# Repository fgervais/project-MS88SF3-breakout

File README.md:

# MS88SF3 Breakout Board

## Objective

Try out the nRF52840 module from Minew.

## Power Consumption

### Sleep - Full RAM retention - GPIO wake-up

Average: 2.78 μA

## Price

## PCB

## BOM

### Firmware

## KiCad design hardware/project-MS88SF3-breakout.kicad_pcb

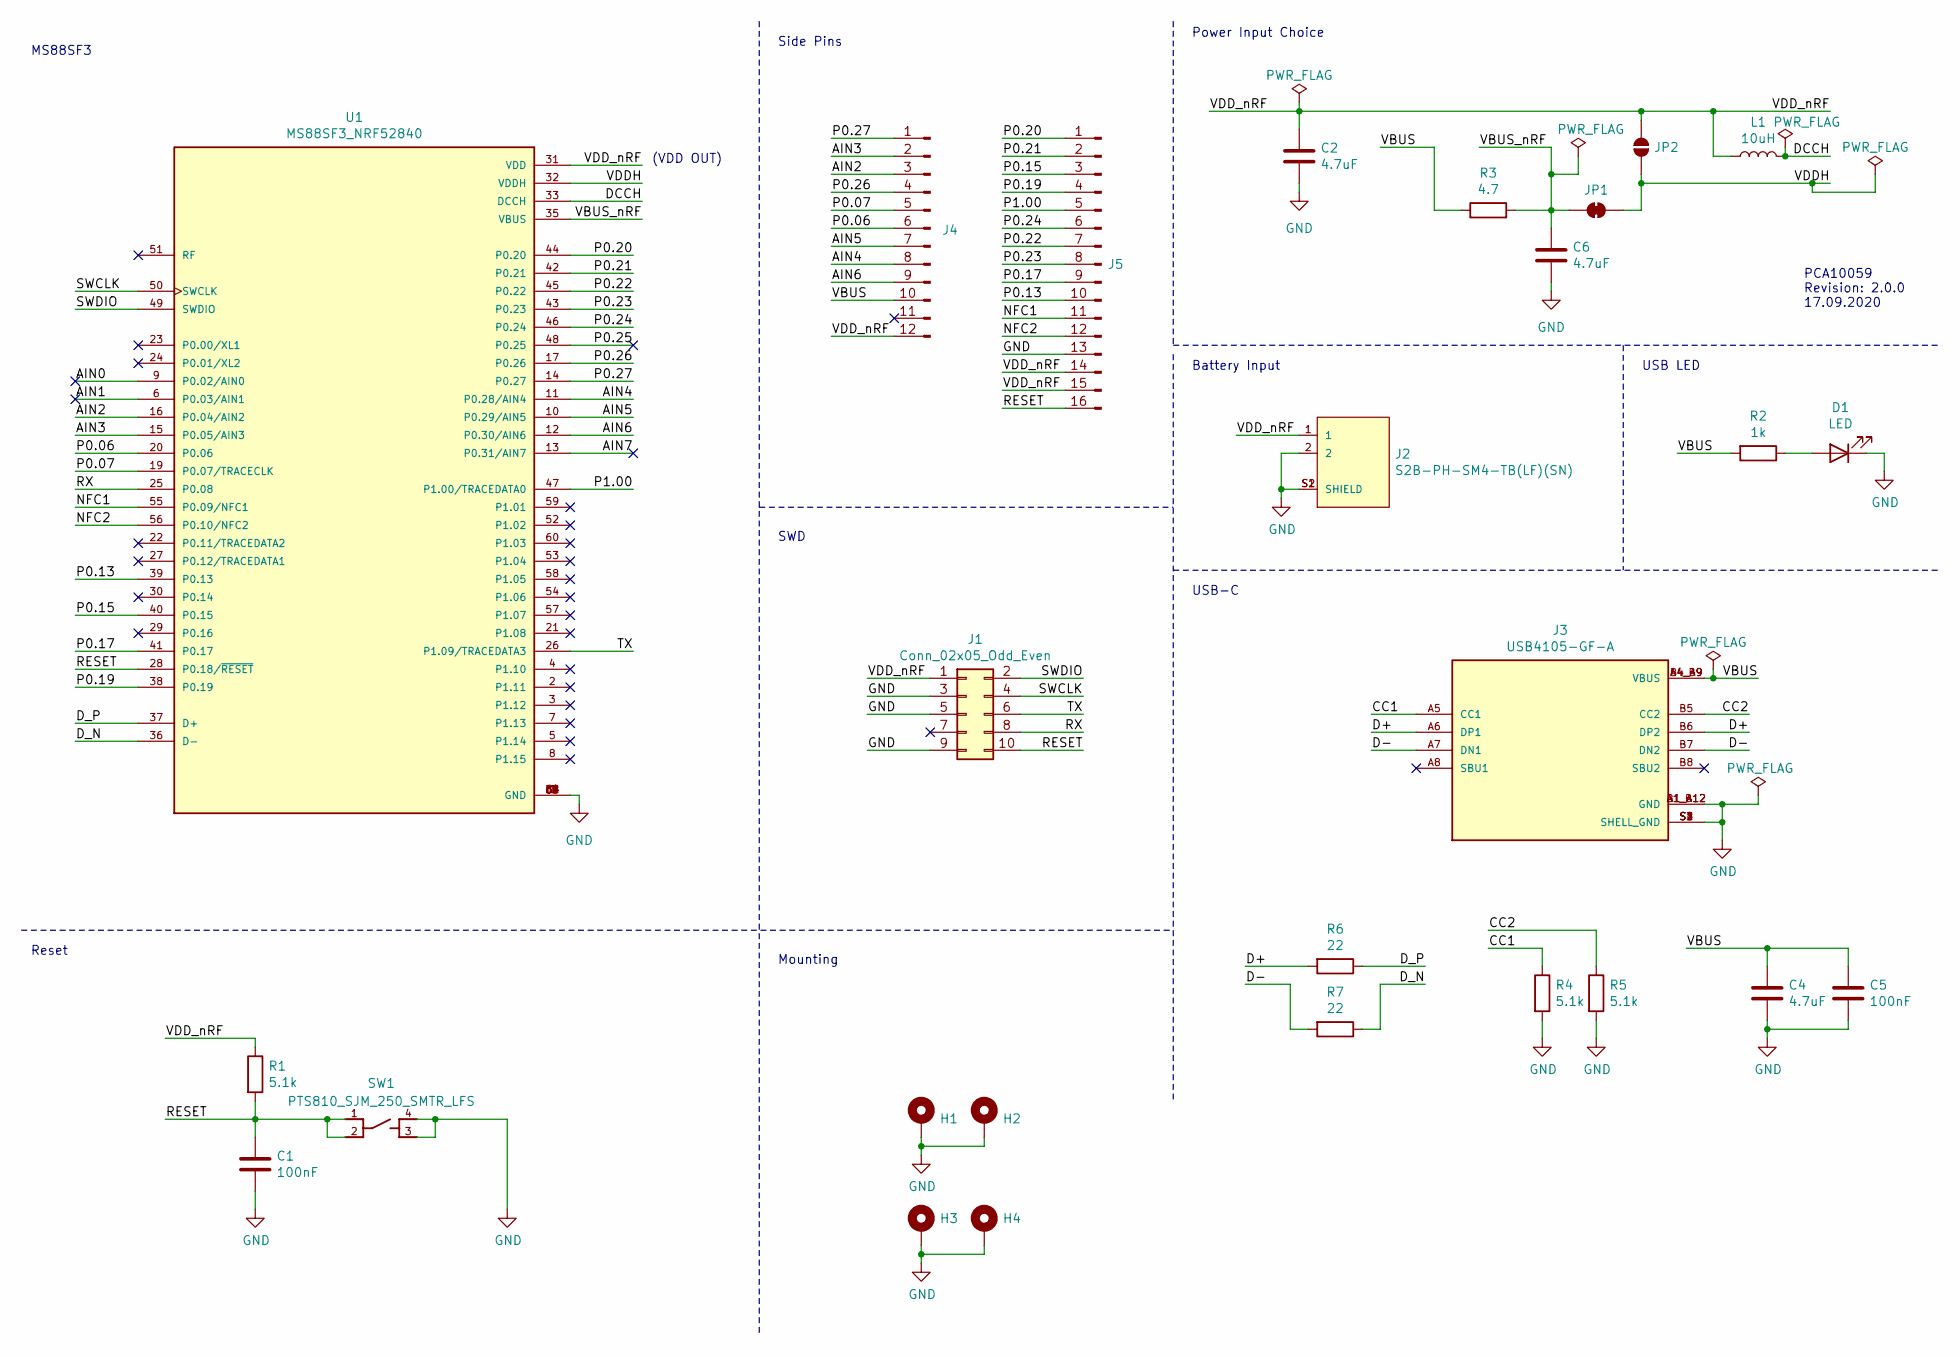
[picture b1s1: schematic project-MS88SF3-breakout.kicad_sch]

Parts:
C1, C5: 100nF; C_0603_1608Metric
C2, C4, C6: 4.7uF; C_0805_2012Metric
D1: LED; LED_0603_1608Metric
H1, H2, H3, H4: MountingHole_Pad; MountingHole_2.2mm_M2_ISO7380_Pad
J1: Conn_02x05_Odd_Even; PinHeader_2x05_P1.27mm_Vertical_SMD
J2: S2B-PH-SM4-TB(LF)(SN); JST_S2B-PH-SM4-TB(LF)(SN)
J3: USB4105-GF-A; GCT_USB4105-GF-A; PARTREV A3
J4: Conn_01x12_Pin; PinHeader_1x12_P2.54mm_Vertical
J5: Conn_01x16_Pin; PinHeader_1x16_P2.54mm_Vertical
JP1: SolderJumper_2_Bridged; SolderJumper-2_P1.3mm_Bridged_RoundedPad1.0x1.5mm
JP2: SolderJumper_2_Open; SolderJumper-2_P1.3mm_Open_RoundedPad1.0x1.5mm
L1: 10uH; L_0603_1608Metric
R1, R4, R5: 5.1k; R_0603_1608Metric
R2: 1k; R_0603_1608Metric
R3: 4.7; R_0603_1608Metric
R6, R7: 22; R_0603_1608Metric
SW1: PTS810_SJM_250_SMTR_LFS; SW_PTS810_SJM_250_SMTR_LFS; DigiKey_Part_Number CKN10502TR-ND
U1: MS88SF3_NRF52840; MODULE_MS88SF3_NRF52840; PARTREV V1.1

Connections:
/AIN0: U1.9 (P0.02/AIN0)
/AIN1: U1.6 (P0.03/AIN1)
/AIN2: J4.3, U1.16 (P0.04/AIN2)
/AIN3: J4.2, U1.15 (P0.05/AIN3)
/AIN4: J4.8, U1.11 (P0.28/AIN4)
/AIN5: J4.7, U1.10 (P0.29/AIN5)
/AIN6: J4.9, U1.12 (P0.30/AIN6)
/AIN7: U1.13 (P0.31/AIN7)
/CC1: J3.A5 (CC1), R4.1
/CC2: J3.B5 (CC2), R5.1
/D+: J3.A6 (DP1), J3.B6 (DP2), R6.2
/D-: J3.A7 (DN1), J3.B7 (DN2), R7.2
/DCCH: L1.2, U1.33 (DCCH)
/D_N: R7.1, U1.36 (D-)
/D_P: R6.1, U1.37 (D+)
/NFC1: J5.11, U1.55 (P0.09/NFC1)
/NFC2: J5.12, U1.56 (P0.10/NFC2)
/P0.06: J4.6, U1.20 (P0.06)
/P0.07: J4.5, U1.19 (P0.07/TRACECLK)
/P0.13: J5.10, U1.39 (P0.13)
/P0.15: J5.3, U1.40 (P0.15)
/P0.17: J5.9, U1.41 (P0.17)
/P0.19: J5.4, U1.38 (P0.19)
/P0.20: J5.1, U1.44 (P0.20)
/P0.21: J5.2, U1.42 (P0.21)
/P0.22: J5.7, U1.45 (P0.22)
/P0.23: J5.8, U1.43 (P0.23)
/P0.24: J5.6, U1.46 (P0.24)
/P0.25: U1.48 (P0.25)
/P0.26: J4.4, U1.17 (P0.26)
/P0.27: J4.1, U1.14 (P0.27)
/P1.00: J5.5, U1.47 (P1.00/TRACEDATA0)
/RESET: C1.1, J1.10, J5.16, R1.2, SW1.1, SW1.2, U1.28 (P0.18/~RESET)
/RX: J1.8, U1.25 (P0.08)
/SWCLK: J1.4, U1.50 (SWCLK)
/SWDIO: J1.2, U1.49 (SWDIO)
/TX: J1.6, U1.26 (P1.09/TRACEDATA3)
/VBUS: C4.1, C5.1, J3.A4_B9 (VBUS), J3.B4_A9 (VBUS), J4.10, R2.2, R3.1
/VBUS_nRF: C6.1, JP1.1 (A), R3.2, U1.35 (VBUS)
/VDDH: JP1.2 (B), JP2.2 (B), U1.32 (VDDH)
/VDD_nRF: C2.1, J1.1, J2.1, J4.12, J5.14, J5.15, JP2.1 (A), L1.1, R1.1, U1.31 (VDD)
GND: C1.2, C2.2, C4.2, C5.2, C6.2, D1.1 (K), H1.1, H2.1, H3.1, H4.1, J1.3, J1.5, J1.9, J2.2, J2.S1 (SHIELD), J2.S2 (SHIELD), J3.A1_B12 (GND), J3.B1_A12 (GND), J3.S1 (SHELL_GND), J3.S2 (SHELL_GND), J3.S3 (SHELL_GND), J3.S4 (SHELL_GND), J5.13, R4.2, R5.2, SW1.3, SW1.4, U1.1 (GND), U1.18 (GND), U1.34 (GND), U1.61 (GND), U1.62 (GND), U1.63 (GND), U1.64 (GND)
unnamed: D1.2 (A), R2.1

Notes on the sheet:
USB LED
Side Pins
SWD
Mounting
PCA10059 Revision: 2.0.0 17.09.2020
Power Input Choice
Battery Input
Reset
USB-C
(VDD OUT)
MS88SF3

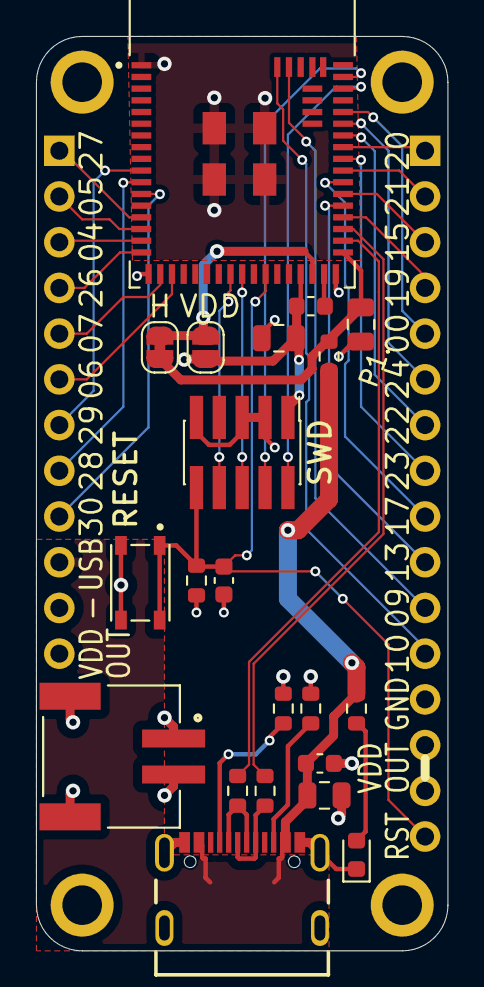
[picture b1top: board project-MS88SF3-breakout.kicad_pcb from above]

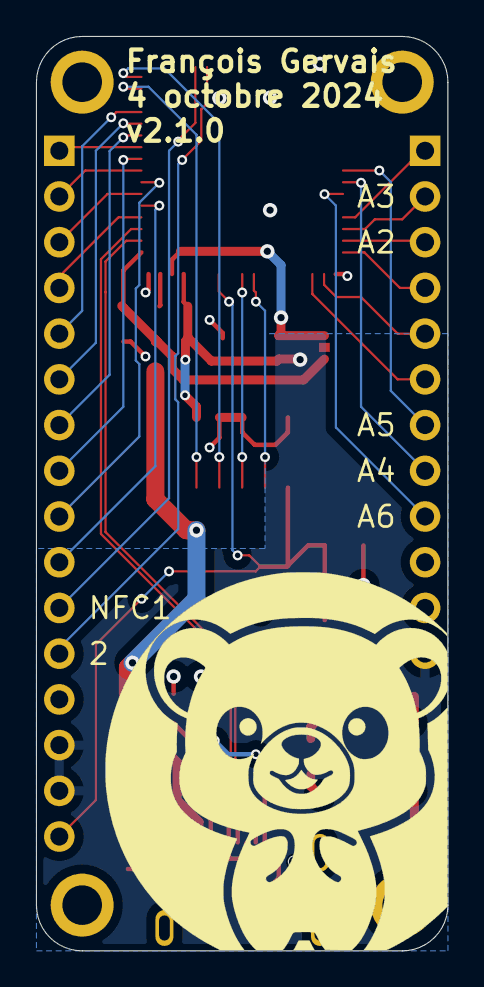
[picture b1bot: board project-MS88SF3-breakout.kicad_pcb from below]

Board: 4 copper layers, 22.9 x 50.8 mm, 28 parts (3 on the bottom side), 39 nets.

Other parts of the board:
Ref**: Val**; bear-body_silk_16x16

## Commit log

2022-07-01 Add library submodule
2022-07-01 Blank project
2022-07-02 Add the MS88SF3 symbol
2022-08-22 Most components added to schematic
2022-08-22 First placement
2022-08-24 Add wires to schematic
2022-08-25 Make it a feather shape
2022-08-25 Change the MS88SF3 module to the nRF52840
2022-08-26 Everything connected
2022-08-26 Half routing done
2022-08-27 USB route
2022-08-27 Routing done
2022-08-28 Clean up schematic
2022-08-29 Ground fill under the module
2022-09-02 Add the bear on the bottom
2022-09-03 Show other layers
2022-09-03 Add gerber files
2022-09-05 Generate gerbers
2022-09-25 Create fab sheet
2022-09-30 Select different layers
2022-10-02 Add images of board
2022-10-02 Remove some titles
2022-10-26 Remove unused vias on VBUS fill
2022-10-26 Remove version on silk
2022-10-26 Upgrade ground fill under module
2022-10-30 Add sleep power information (2.78uA)
2022-10-30 Add power value
2023-02-25 Add edge cut svg
2023-08-29 Add datasheet
2023-09-19 Update images
2024-04-25 Add PTS810-SJM-250-SMTR-LFS
2024-04-26 New project format
2024-04-26 Update obsolete connectors
2024-04-26 Unrescue pwr_flag and gnd
2024-04-26 Ignore backups and lock file
2024-04-26 Fix ERC error
2024-04-26 Change reset button
2024-04-26 User SolderJumper-2 footprint without center soldermask
2024-04-26 Move TX to SWO
2024-04-27 Change header RX/TX to gpios
2024-04-27 Change swd RX/TX to easier pins to route
2024-04-27 Open pcb and save
2024-04-27 Fill pours and run DRC
2024-04-27 Update pcb from schematic
2024-04-27 Remove unused traces
2024-04-28 Change 12/16 pin header footprint
2024-04-28 Update pin headers from schematic
2024-04-28 Place new button
2024-04-28 Change old RX/TX pin silkscreen
2024-04-28 Send all alternate silkscreen to the back
2024-04-28 Route all nets
2024-04-28 Bring back the panda
2024-04-28 Run DRC
2024-04-28 Add the gerbers zip file
    I think this is the zip I used to have the pink boards made.
2024-04-28 Run schematic ERC
2024-04-28 Update date silkscreen
2024-04-28 Make part of VDDH trace smaller
2024-04-28 Update active layers
2024-04-28 Update DRC exclusions
2024-04-28 Add the silkscreen version of the previous commit
2024-04-28 Remove obsolete files
2024-04-29 Remove solder mask expansion from button footprint
2024-04-29 Make smoother VBUS pad entry
2024-04-29 Update the solder jumpers
2024-04-29 Remove v1 gerbers
2024-04-29 Update version on silkscreen
2024-10-03 Save with current kicad version
2024-10-03 Update half the pins in the schematic
2024-10-04 Finish routing
2024-10-05 Finish back side silkscreen
2024-10-05 Finish front side silkscreen
